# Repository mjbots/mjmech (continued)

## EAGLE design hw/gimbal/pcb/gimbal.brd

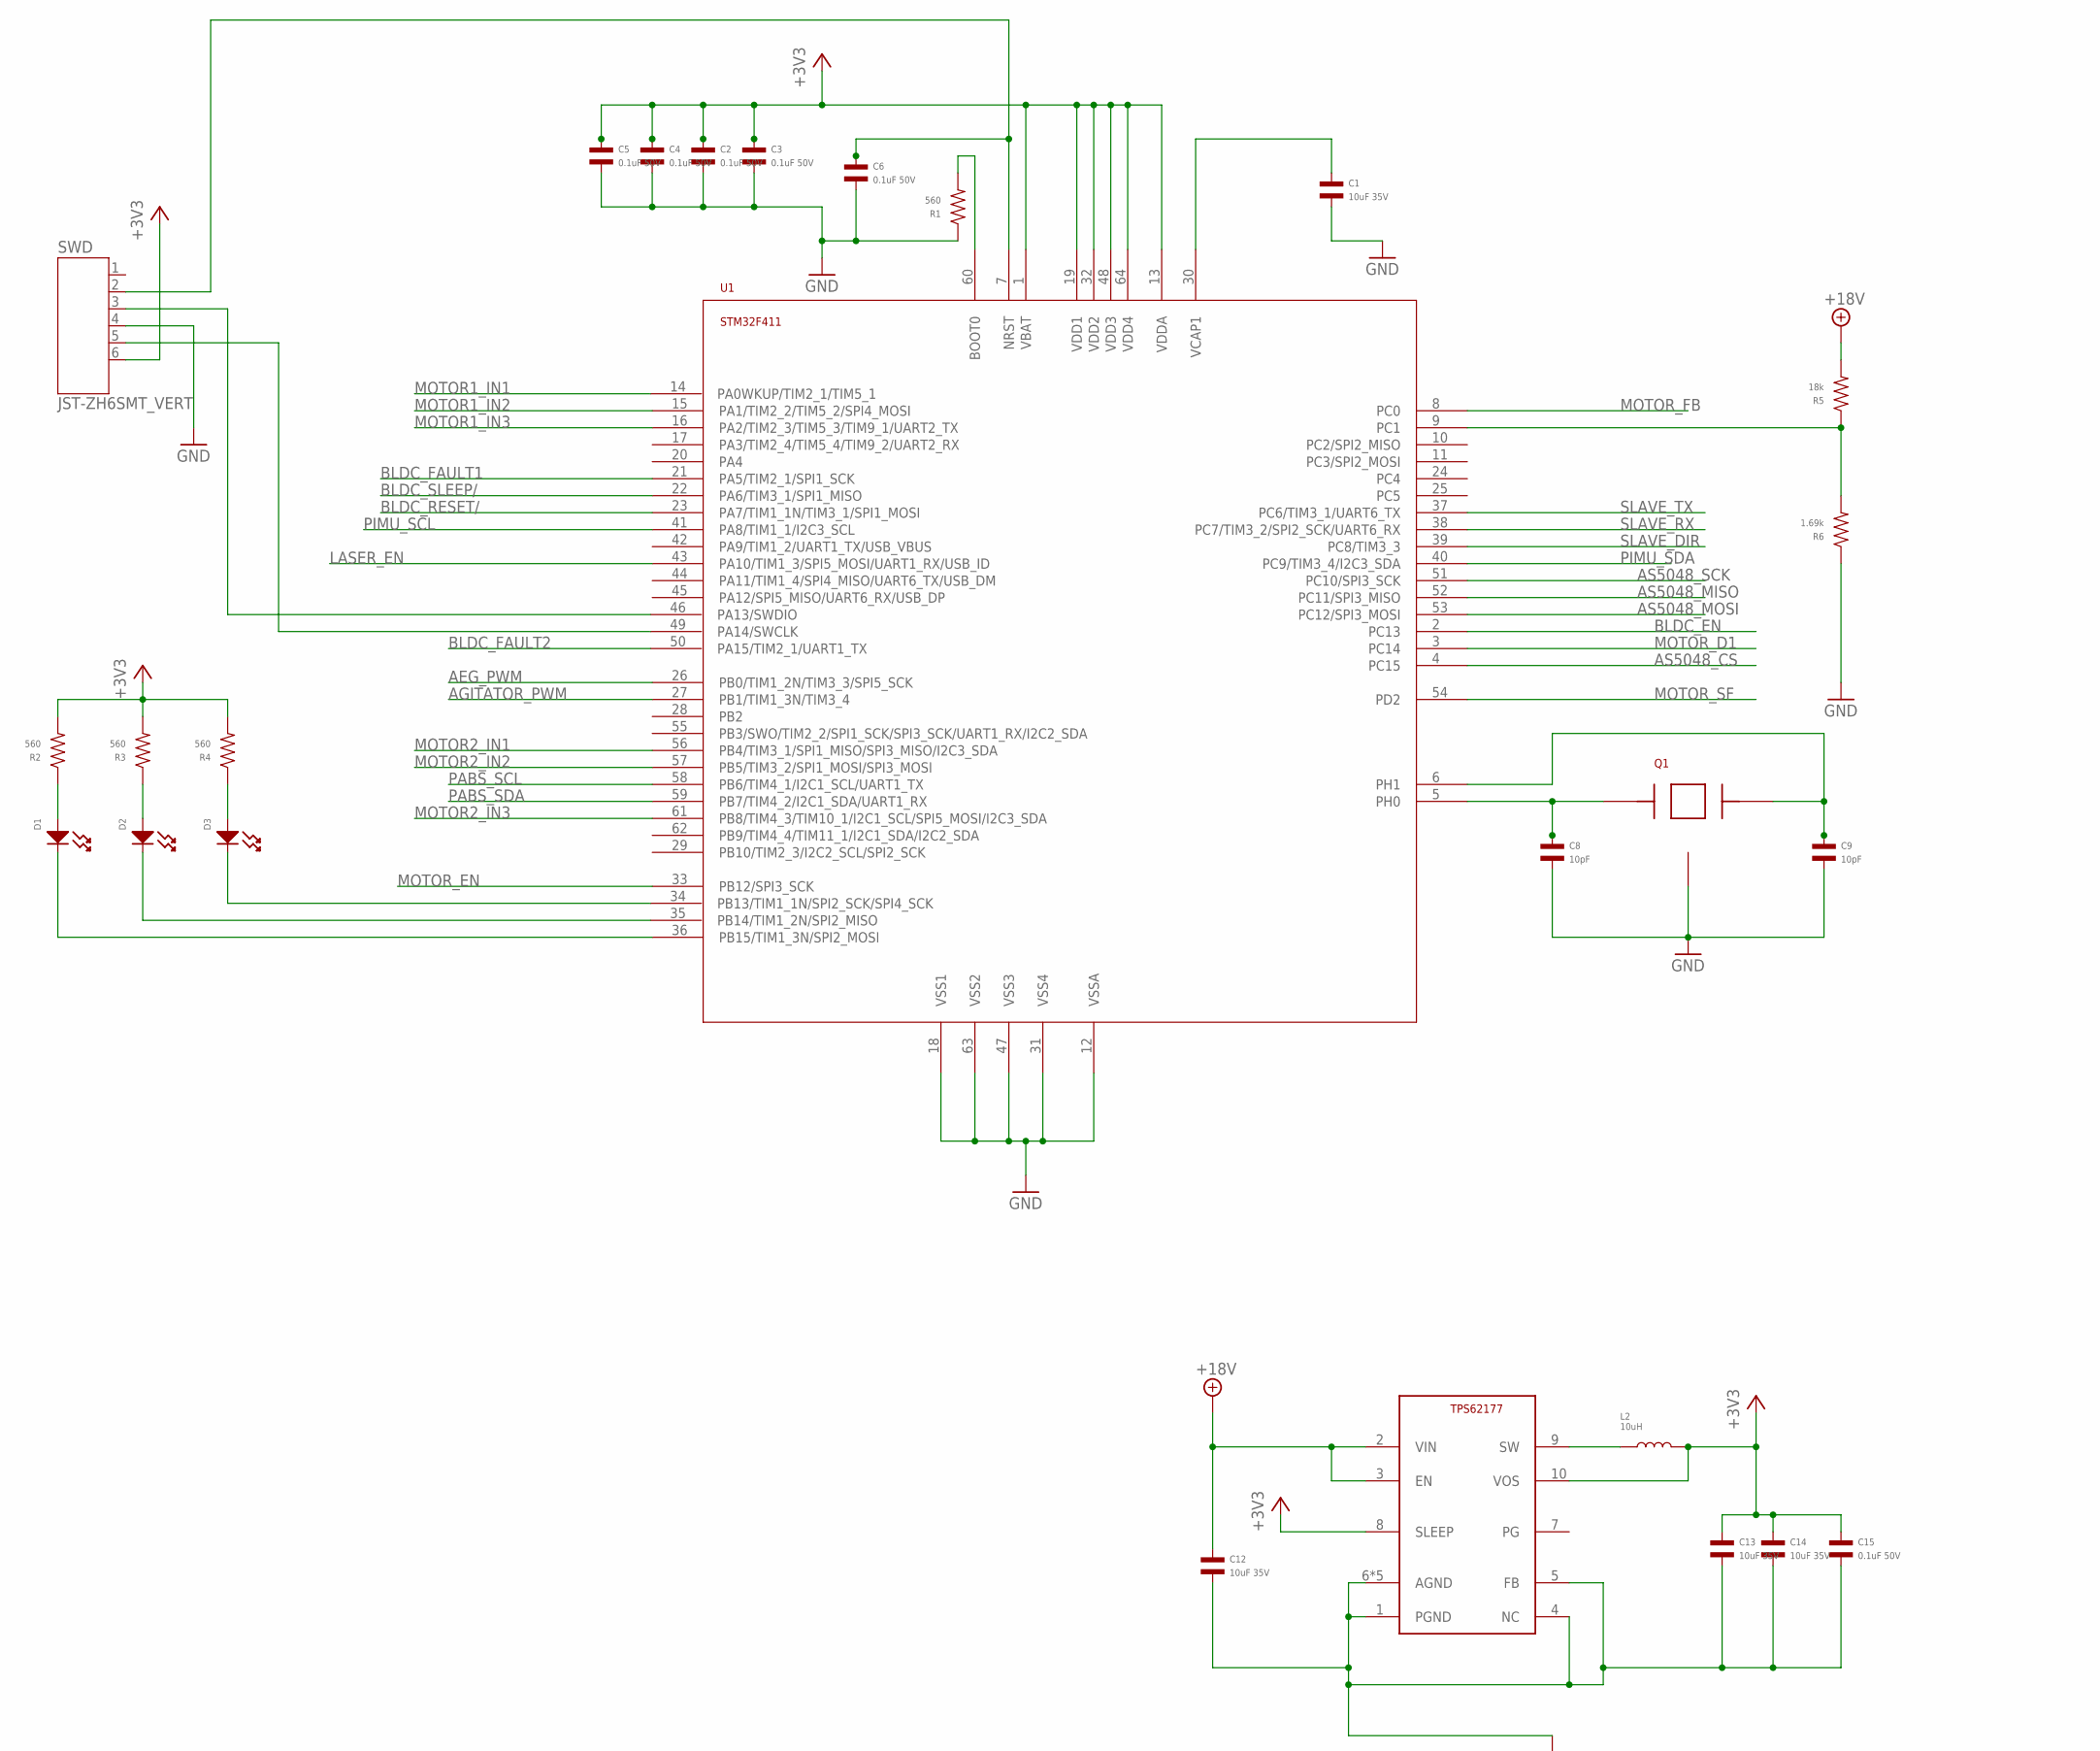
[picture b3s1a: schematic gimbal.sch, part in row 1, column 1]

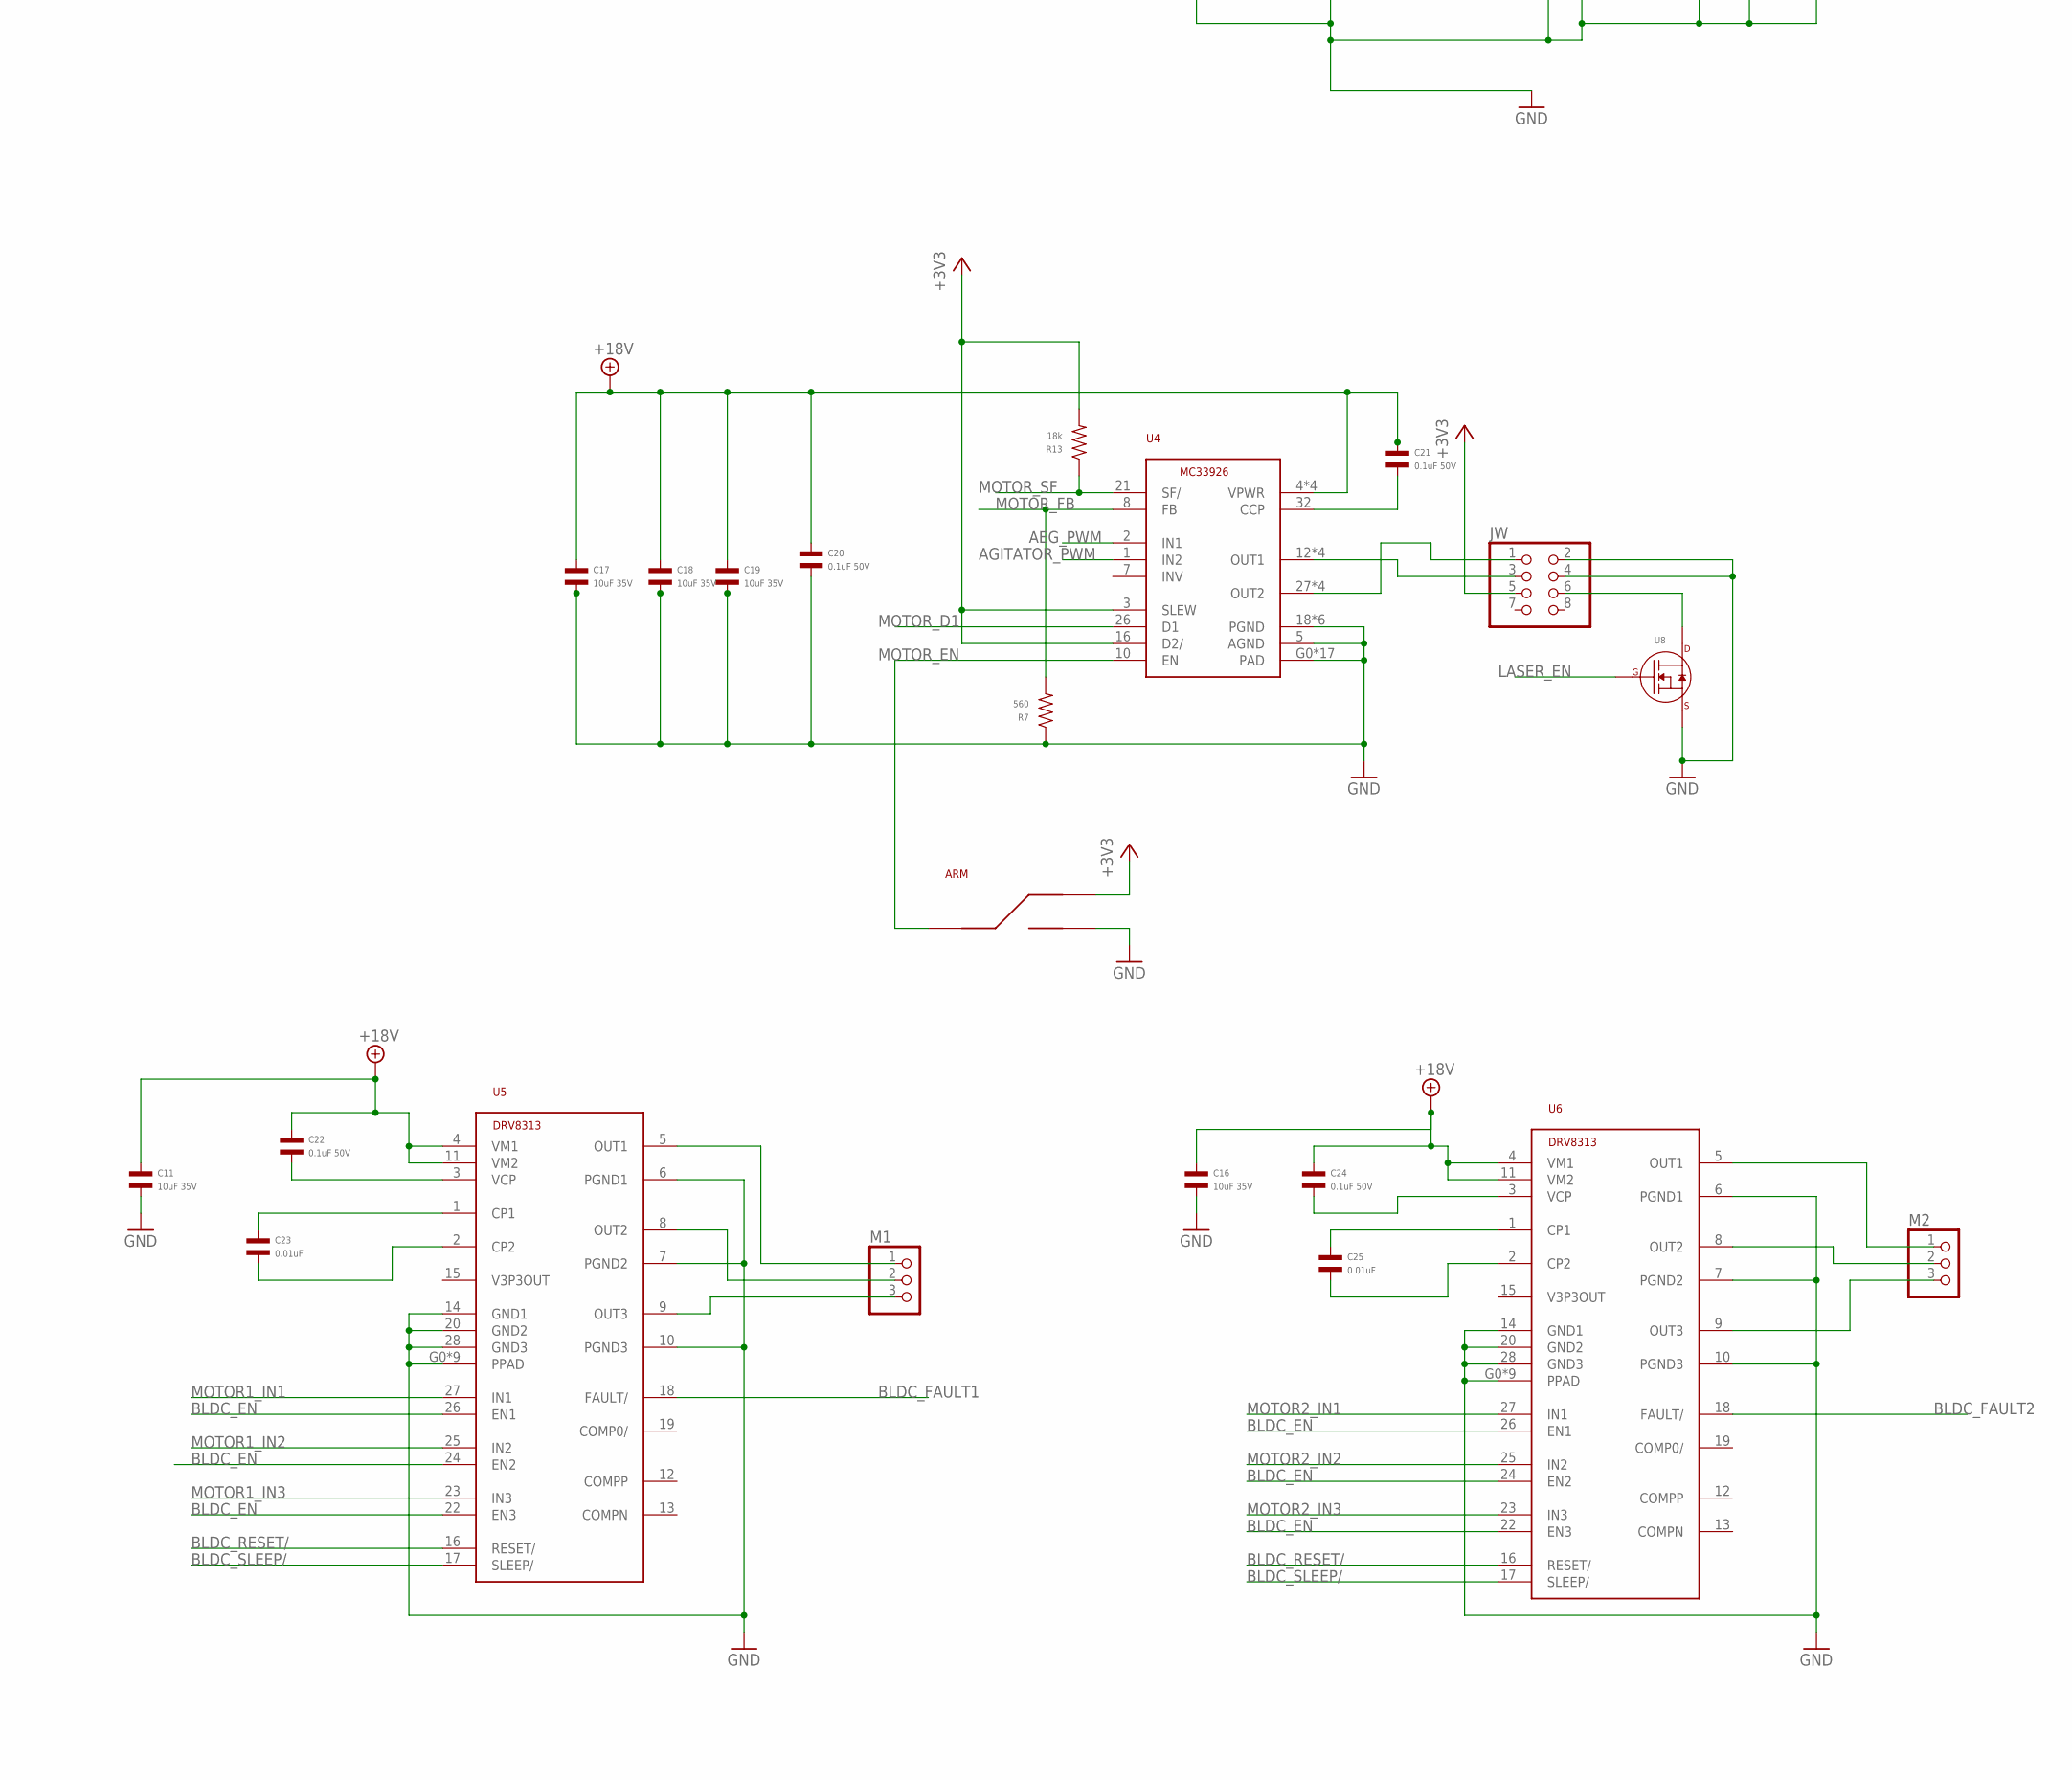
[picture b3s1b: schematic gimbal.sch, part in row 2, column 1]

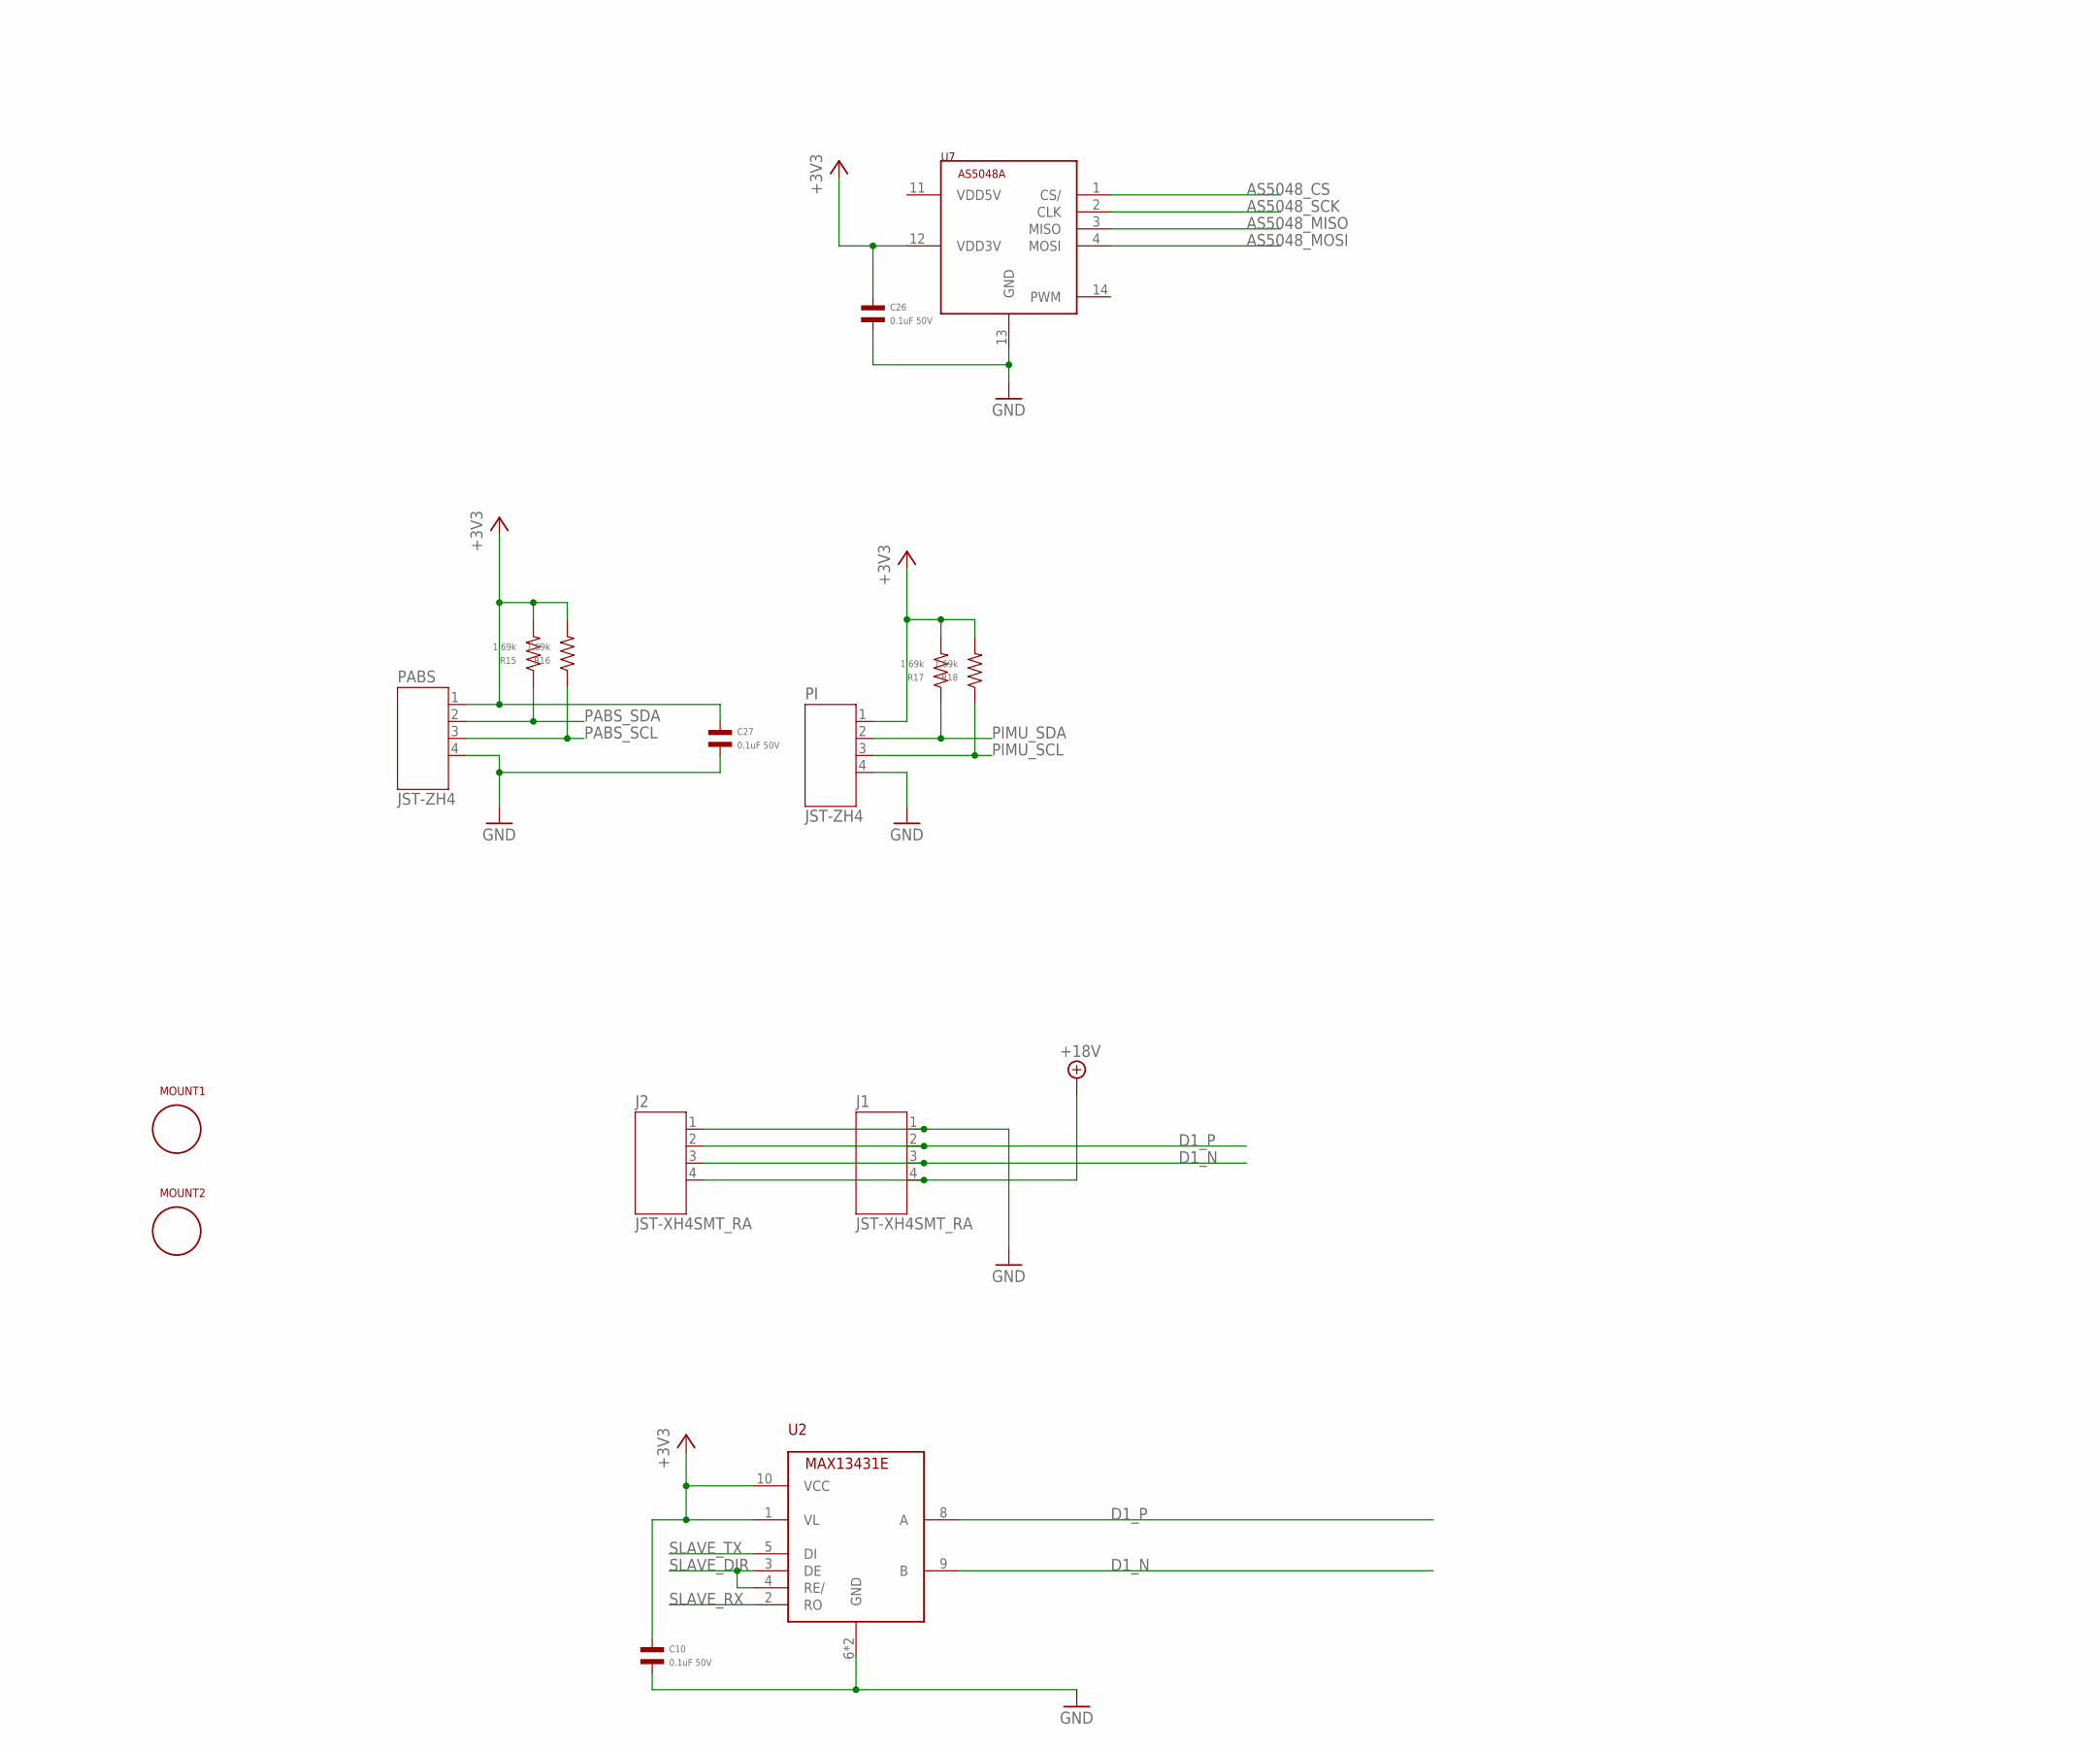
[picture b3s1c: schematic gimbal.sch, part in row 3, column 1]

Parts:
ARM: SLIDE_SWITCHJS_SUB_SWITCH; JS_SUB_SWITCH; MPN JS102011SAQN
C1, C11, C12, C13, C14, C16, C17, C18, C19: 10uF 35V; C1206; MPN CGA5L1X7R1V106M160AE
C2, C3, C4, C5, C6, C10, C15, C20, C21, C22, C24, C26, C27: 0.1uF 50V; C0402; MPN 0402B104K500CT
C8, C9: 10pF; C0603; MPN MF-CAP-0603-10pF
C23, C25: 0.01uF; C0603; MPN MF-CAP-0603-0.01uF
D1, D2, D3: LED_SINGLE-0603-RED; LED0603
J1, J2: JST-XH4SMT_RA; JST_XH_SMT_RA_4; MPN S4B-XH-SM4-TB(LF)(SN)
JW: PINHD-2X4; 2X04
L2: 10uH; L1210; MPN MF-IND-1210-10uH
M1, M2: PINHD-1X3; 1X03
MOUNT1, MOUNT2: M3_MOTOR_MOUNT
PABS: JST-ZH4; JST_ZH_SMT_VERT_4; MPN B4B-ZR-SM4-TF(LF)(SN)
PI: JST-ZH4; JST_ZH_SMT_VERT_4; MPN B4B-ZR-SM4-TF(LF)(SN)
Q1: CRYSTALABM3B; ABM3B; MPN ABM3B-8.000MHZ-10-1-U-T
R1, R2, R3, R4, R7: 560; R0603; MPN MF-RES-0603-560
R5, R13: 18k; R0603; MPN MF-RES-0603-18K
R6, R15, R16, R17, R18: 1.69k; R0603; MPN MF-RES-0603-1.69K
SWD: JST-ZH6SMT_VERT; JST_B6B-ZR-SM4-TF(LF)(SN); MPN B6B-ZR-SM4-TF(LF)(SN)
U1: STM32F4R_64PIN; LQFP64; MPN STM32F411RET6
U2: MAX13431E; TDFN10; MPN MAX13431EETB+T
U3: TPS62177WSON10; WSON10; MPN TPS62177DQCR
U4: MC33926; PQFN32; MPN MC33926PNBR2
U5, U6: DRV8313; HTSSOP28; MPN DRV8313PWP
U7: AS5048A; TSSOP14; MPN AS5047P-ATSM
U8: N-CHANNEL_FET_SOT-23-3; SOT-23-3; MPN MF-DSC-SOT233-BSS138

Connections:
+3V3: ARM.1, C2.P$1, C3.P$1, C4.P$1, C5.P$1, C10.P$1, C13.P$1, C14.P$1, C15.P$1, C26.P$1, C27.P$1, JW.5, L2.P$2, PABS.1, PI.1, R2.P$2, R3.P$2, R4.P$2, R13.P$2, R15.P$2, R16.P$2, R17.P$2, R18.P$2, SWD.6, U1.1 (VBAT), U1.13 (VDDA), U1.19 (VDD1), U1.32 (VDD2), U1.48 (VDD3), U1.64 (VDD4), U2.1 (VL), U2.10 (VCC), U3.8 (SLEEP), U3.10 (VOS), U4.3 (SLEW), U4.16 (D2/), U7.12 (VDD3V)
+18V: C11.P$1, C12.P$1, C16.P$1, C17.P$1, C18.P$1, C19.P$1, C20.P$1, C21.P$1, C22.P$1, C24.P$1, J1.4, J2.4, R5.P$2, U3.2 (VIN), U3.3 (EN), U4.4 (VPWR), U4.6 (VPWR), U4.11 (VPWR), U4.31 (VPWR), U5.4 (VM1), U5.11 (VM2), U6.4 (VM1), U6.11 (VM2)
AEG_PWM: U1.26 (PB0/TIM1_2N/TIM3_3/SPI5_SCK), U4.2 (IN1)
AGITATOR_PWM: U1.27 (PB1/TIM1_3N/TIM3_4), U4.1 (IN2)
AS5048_CS: U1.4 (PC15), U7.1 (CS/)
AS5048_MISO: U1.52 (PC11/SPI3_MISO), U7.3 (MISO)
AS5048_MOSI: U1.53 (PC12/SPI3_MOSI), U7.4 (MOSI)
AS5048_SCK: U1.51 (PC10/SPI3_SCK), U7.2 (CLK)
BLDC_EN: U1.2 (PC13), U5.22 (EN3), U5.24 (EN2), U5.26 (EN1), U6.22 (EN3), U6.24 (EN2), U6.26 (EN1)
BLDC_FAULT1: U1.21 (PA5/TIM2_1/SPI1_SCK), U5.18 (FAULT/)
BLDC_FAULT2: U1.50 (PA15/TIM2_1/UART1_TX), U6.18 (FAULT/)
BLDC_RESET/: U1.23 (PA7/TIM1_1N/TIM3_1/SPI1_MOSI), U5.16 (RESET/), U6.16 (RESET/)
BLDC_SLEEP/: U1.22 (PA6/TIM3_1/SPI1_MISO), U5.17 (SLEEP/), U6.17 (SLEEP/)
D1_N: J1.3, J2.3, U2.9 (B)
D1_P: J1.2, J2.2, U2.8 (A)
GND: ARM.3, C1.P$2, C2.P$2, C3.P$2, C4.P$2, C5.P$2, C6.P$2, C8.P$2, C9.P$2, C10.P$2, C11.P$2, C12.P$2, C13.P$2, C14.P$2, C15.P$2, C16.P$2, C17.P$2, C18.P$2, C19.P$2, C20.P$2, C26.P$2, C27.P$2, J1.1, J2.1, JW.2, JW.4, PABS.4, PI.4, Q1.2, Q1.4, R1.P$1, R6.P$1, R7.P$1, SWD.4, U1.12 (VSSA), U1.18 (VSS1), U1.31 (VSS4), U1.47 (VSS3), U1.63 (VSS2), U2.6 (GND), U2.PAD (GND), U3.1 (PGND), U3.4 (NC), U3.5 (FB), U3.6 (AGND), U3.P0 (AGND), U3.P1 (AGND), U3.P2 (AGND), U3.P3 (AGND), U4.5 (AGND), U4.18 (PGND), U4.19 (PGND), U4.20 (PGND), U4.22 (PGND), U4.23 (PGND), U4.24 (PGND), U4.G0 (PAD), U4.G1 (PAD), U4.G2 (PAD), U4.G3 (PAD), U4.G4 (PAD), U4.G5 (PAD), U4.G6 (PAD), U4.G7 (PAD), U4.G8 (PAD), U4.G9 (PAD), U4.G10 (PAD), U4.G11 (PAD), U4.G12 (PAD), U4.G13 (PAD), U4.G14 (PAD), U4.G15 (PAD), U4.G16 (PAD), U5.6 (PGND1), U5.7 (PGND2), U5.10 (PGND3), U5.14 (GND1), U5.20 (GND2), U5.28 (GND3), U5.G0 (PPAD), U5.G1 (PPAD), U5.G2 (PPAD), U5.G3 (PPAD), U5.G4 (PPAD), U5.G5 (PPAD), U5.G6 (PPAD), U5.G7 (PPAD), U5.G8 (PPAD), U6.6 (PGND1), U6.7 (PGND2), U6.10 (PGND3), U6.14 (GND1), U6.20 (GND2), U6.28 (GND3), U6.G0 (PPAD), U6.G1 (PPAD), U6.G2 (PPAD), U6.G3 (PPAD), U6.G4 (PPAD), U6.G5 (PPAD), U6.G6 (PPAD), U6.G7 (PPAD), U6.G8 (PPAD), U7.13 (GND), U8.P$2 (SOURCE)
LASER_EN: U1.43 (PA10/TIM1_3/SPI5_MOSI/UART1_RX/USB_ID), U8.P$1 (GATE)
MOTOR1_IN1: U1.14 (PA0WKUP/TIM2_1/TIM5_1), U5.27 (IN1)
MOTOR1_IN2: U1.15 (PA1/TIM2_2/TIM5_2/SPI4_MOSI), U5.25 (IN2)
MOTOR1_IN3: U1.16 (PA2/TIM2_3/TIM5_3/TIM9_1/UART2_TX), U5.23 (IN3)
MOTOR2_IN1: U1.56 (PB4/TIM3_1/SPI1_MISO/SPI3_MISO/I2C3_SDA), U6.27 (IN1)
MOTOR2_IN2: U1.57 (PB5/TIM3_2/SPI1_MOSI/SPI3_MOSI), U6.25 (IN2)
MOTOR2_IN3: U1.61 (PB8/TIM4_3/TIM10_1/I2C1_SCL/SPI5_MOSI/I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), U6.23 (IN3)
MOTOR_D1: U1.3 (PC14), U4.26 (D1)
MOTOR_EN: ARM.2, U1.33 (PB12/SPI3_SCK), U4.10 (EN)
MOTOR_FB: R7.P$2, U1.8 (PC0), U4.8 (FB)
MOTOR_SF: R13.P$1, U1.54 (PD2), U4.21 (SF/)
unnamed: JW.6, U8.P$3 (DRAIN)
unnamed: JW.3, U4.12 (OUT1), U4.13 (OUT1), U4.14 (OUT1), U4.15 (OUT1)
unnamed: JW.1, U4.27 (OUT2), U4.28 (OUT2), U4.29 (OUT2), U4.30 (OUT2)
unnamed: L2.P$1, U3.9 (SW)
unnamed: C21.P$2, U4.32 (CCP)
unnamed: M1.1, U5.5 (OUT1)
unnamed: M1.2, U5.8 (OUT2)
unnamed: M1.3, U5.9 (OUT3)
unnamed: M2.1, U6.5 (OUT1)
unnamed: M2.2, U6.8 (OUT2)
unnamed: M2.3, U6.9 (OUT3)
unnamed: C1.P$1, U1.30 (VCAP1)
unnamed: C6.P$1, SWD.2, U1.7 (NRST)
unnamed: C25.P$1, U6.1 (CP1)
unnamed: C25.P$2, U6.2 (CP2)
unnamed: C23.P$2, U5.2 (CP2)
unnamed: C23.P$1, U5.1 (CP1)
unnamed: C22.P$2, U5.3 (VCP)
unnamed: C24.P$2, U6.3 (VCP)
unnamed: SWD.5, U1.49 (PA14/SWCLK)
unnamed: SWD.3, U1.46 (PA13/SWDIO)
unnamed: R1.P$2, U1.60 (BOOT0)
unnamed: R5.P$1, R6.P$2, U1.9 (PC1)
unnamed: C8.P$1, Q1.1, U1.5 (PH0)
unnamed: C9.P$1, Q1.3, U1.6 (PH1)
unnamed: D2.CATHODE, U1.35 (PB14/TIM1_2N/SPI2_MISO)
unnamed: D1.ANODE, R2.P$1
unnamed: D2.ANODE, R3.P$1
unnamed: D3.ANODE, R4.P$1
unnamed: D3.CATHODE, U1.34 (PB13/TIM1_1N/SPI2_SCK/SPI4_SCK)
unnamed: D1.CATHODE, U1.36 (PB15/TIM1_3N/SPI2_MOSI)
PABS_SCL: PABS.3, R16.P$1, U1.58 (PB6/TIM4_1/I2C1_SCL/UART1_TX)
PABS_SDA: PABS.2, R15.P$1, U1.59 (PB7/TIM4_2/I2C1_SDA/UART1_RX)
PIMU_SCL: PI.3, R18.P$1, U1.41 (PA8/TIM1_1/I2C3_SCL)
PIMU_SDA: PI.2, R17.P$1, U1.40 (PC9/TIM3_4/I2C3_SDA)
SLAVE_DIR: U1.39 (PC8/TIM3_3), U2.3 (DE), U2.4 (RE/)
SLAVE_RX: U1.38 (PC7/TIM3_2/SPI2_SCK/UART6_RX), U2.2 (RO)
SLAVE_TX: U1.37 (PC6/TIM3_1/UART6_TX), U2.5 (DI)

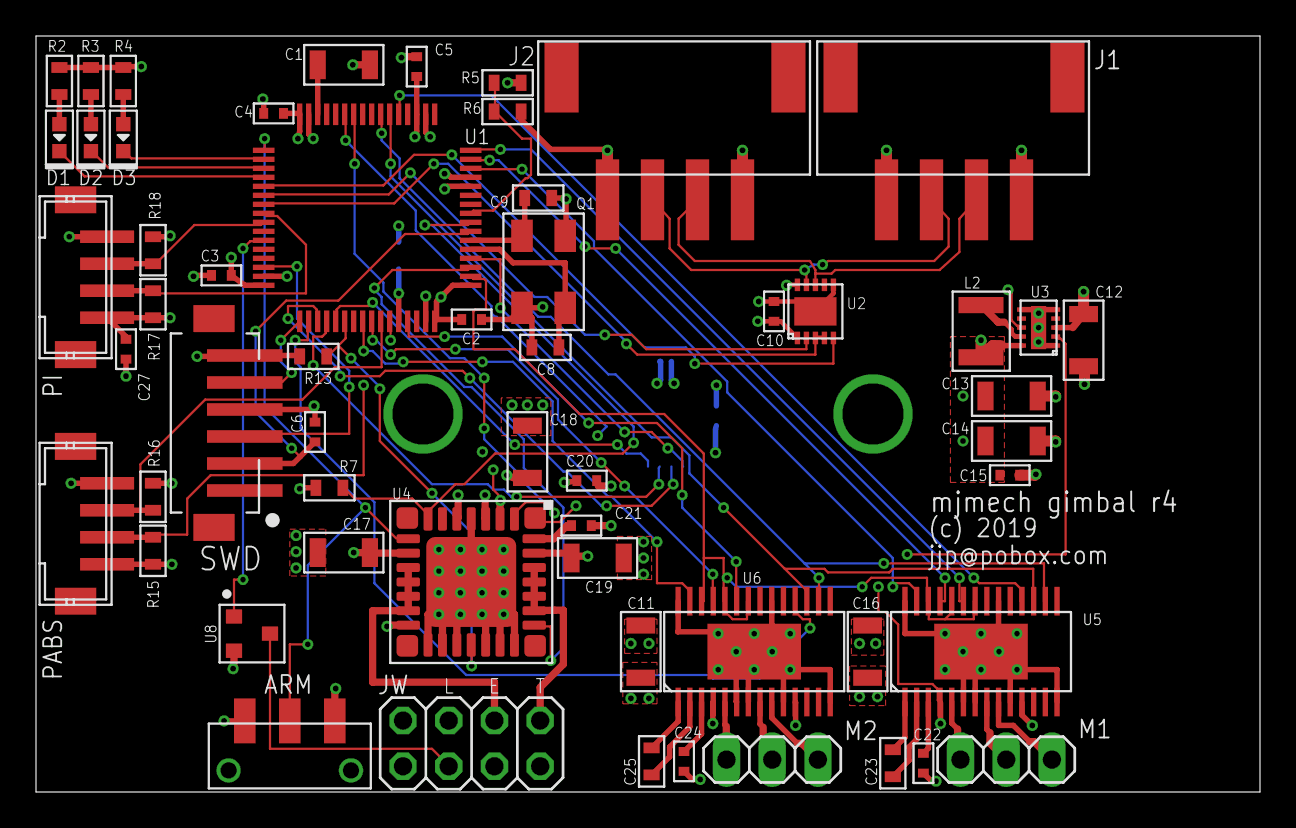
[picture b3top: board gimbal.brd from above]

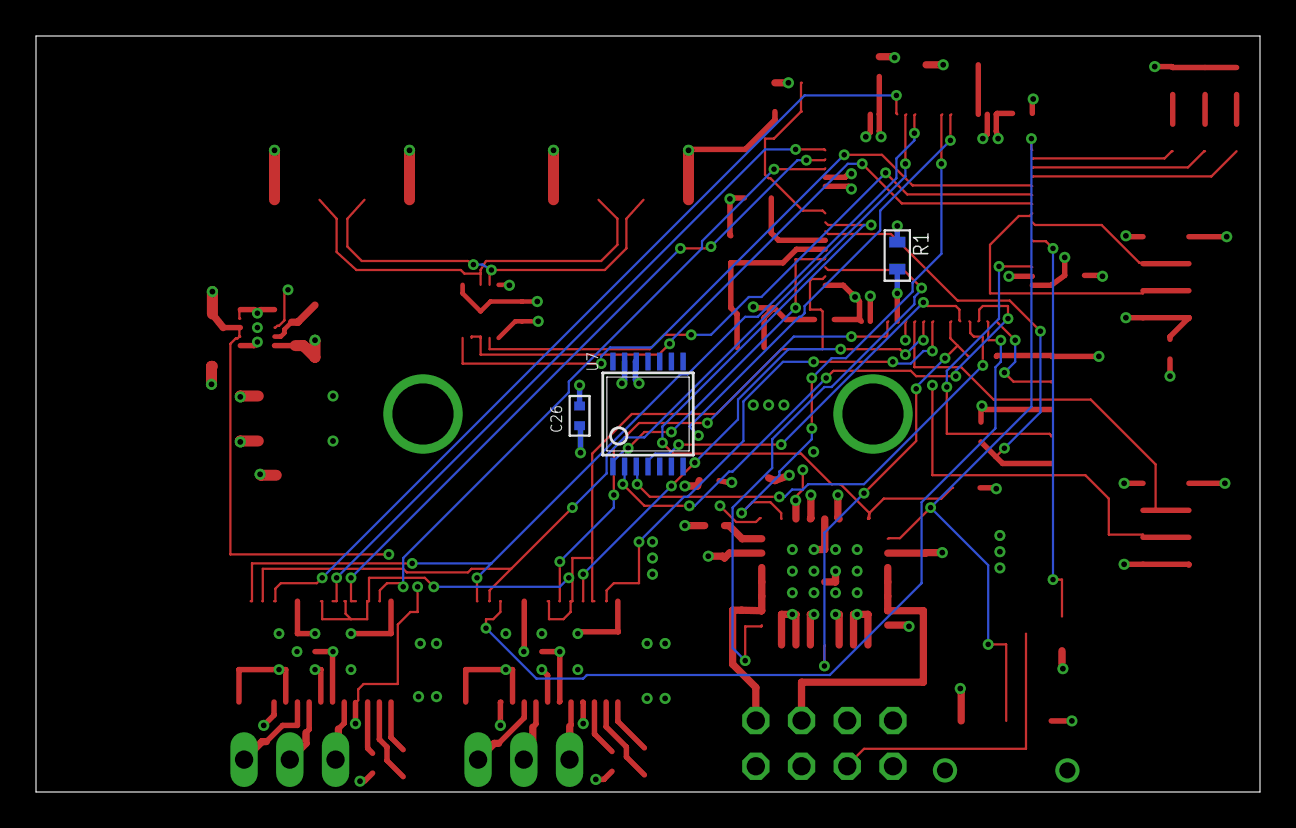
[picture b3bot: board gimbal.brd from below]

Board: 4 copper layers, 68.0 x 42.0 mm, 62 parts (3 on the bottom side), 65 nets.

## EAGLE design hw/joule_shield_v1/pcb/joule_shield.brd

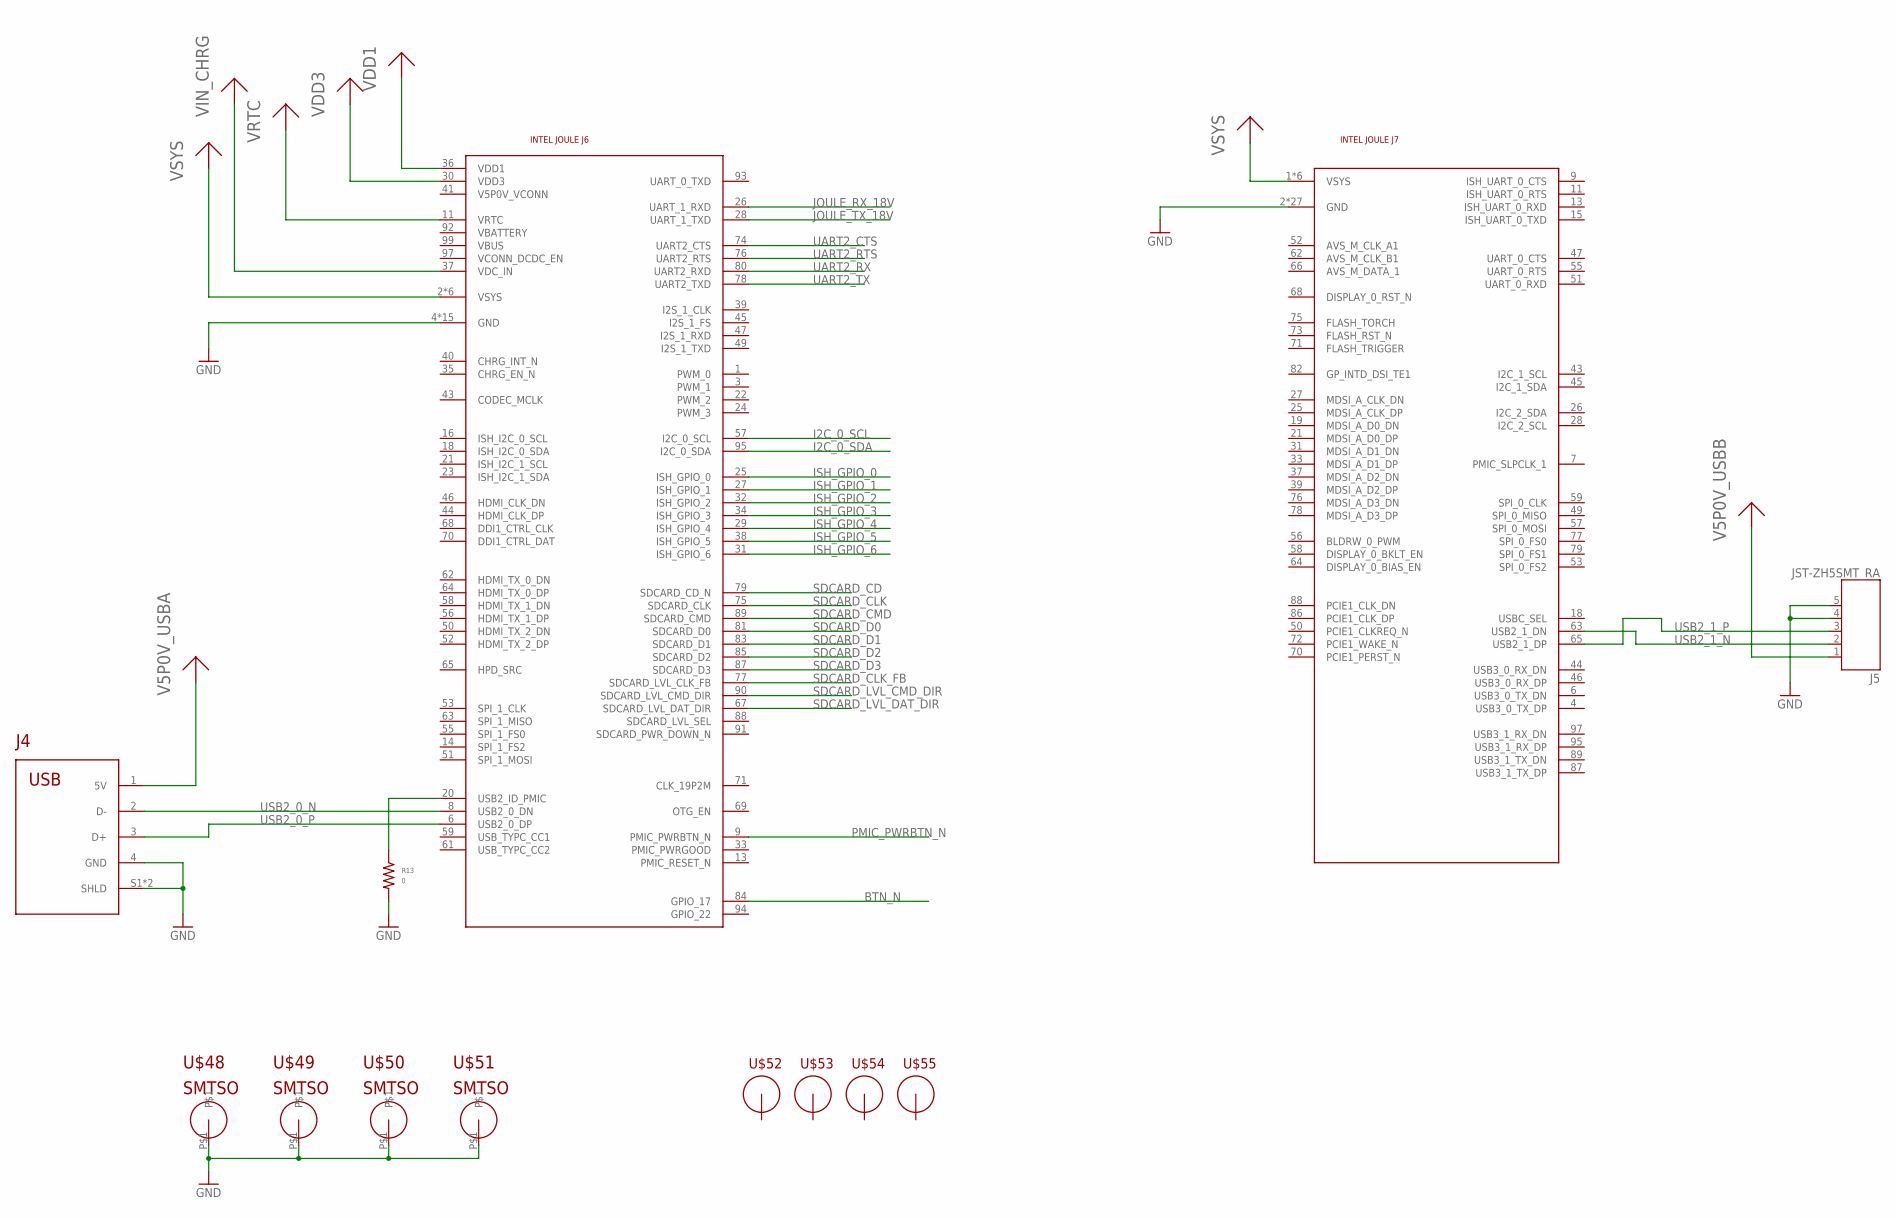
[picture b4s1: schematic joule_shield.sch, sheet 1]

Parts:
J4: USB_AUSB_A_SMT_RA; USB_RECPT_87583; MPN 87583-2010BLF
J5: JST-ZH5SMT_RA; JST_ZH_SMT_RA_5; MPN S5B-ZR-SM4A-TF(LF)(SN)
J6: INTEL_JOULE_J6; HIROSE-40C-100DS; MPN DF40C-100DS-0.4V(51)
J7: INTEL_JOULE_J7; HIROSE-40C-100DS; MPN DF40C-100DS-0.4V(51)
R13: 0; R0603; MPN MF-RES-0603-0
U$48, U$49, U$50, U$51: SMTSOSMTSO-M1.6; SMTSO-M1.6
U$52, U$53, U$54, U$55: M2.5MOUNT

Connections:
BTN_N: J6.84 (GPIO_17); also elsewhere on the board
GND: J4.4 (GND), J4.S1 (SHLD), J4.S2 (SHLD), J5.4, J5.5, J6.4 (GND), J6.10 (GND), J6.19 (GND), J6.42 (GND), J6.48 (GND), J6.54 (GND), J6.60 (GND), J6.66 (GND), J6.72 (GND), J6.73 (GND), J6.82 (GND), J6.86 (GND), J6.96 (GND), J6.98 (GND), J6.100 (GND), J7.2 (GND), J7.5 (GND), J7.8 (GND), J7.10 (GND), J7.16 (GND), J7.17 (GND), J7.23 (GND), J7.24 (GND), J7.29 (GND), J7.30 (GND), J7.35 (GND), J7.36 (GND), J7.41 (GND), J7.42 (GND), J7.54 (GND), J7.60 (GND), J7.61 (GND), J7.67 (GND), J7.74 (GND), J7.80 (GND), J7.84 (GND), J7.85 (GND), J7.90 (GND), J7.91 (GND), J7.93 (GND), J7.96 (GND), J7.99 (GND), R13.P$2, U$48.P$1, U$49.P$1, U$50.P$1, U$51.P$1; also elsewhere on the board
I2C_0_SCL: J6.57 (I2C_0_SCL); also elsewhere on the board
I2C_0_SDA: J6.95 (I2C_0_SDA); also elsewhere on the board
ISH_GPIO_0: J6.25 (ISH_GPIO_0); also elsewhere on the board
ISH_GPIO_1: J6.27 (ISH_GPIO_1); also elsewhere on the board
ISH_GPIO_2: J6.32 (ISH_GPIO_2); also elsewhere on the board
ISH_GPIO_3: J6.34 (ISH_GPIO_3); also elsewhere on the board
ISH_GPIO_4: J6.29 (ISH_GPIO_4); also elsewhere on the board
ISH_GPIO_5: J6.38 (ISH_GPIO_5); also elsewhere on the board
ISH_GPIO_6: J6.31 (ISH_GPIO_6); also elsewhere on the board
JOULE_RX_18V: J6.26 (UART_1_RXD); also elsewhere on the board
JOULE_TX_18V: J6.28 (UART_1_TXD); also elsewhere on the board
unnamed: J6.20 (USB2_ID_PMIC), R13.P$1
PMIC_PWRBTN_N: J6.9 (PMIC_PWRBTN_N); also elsewhere on the board
SDCARD_CD: J6.79 (SDCARD_CD_N); also elsewhere on the board
SDCARD_CLK: J6.75 (SDCARD_CLK); also elsewhere on the board
SDCARD_CLK_FB: J6.77 (SDCARD_LVL_CLK_FB); also elsewhere on the board
SDCARD_CMD: J6.89 (SDCARD_CMD); also elsewhere on the board
SDCARD_D0: J6.81 (SDCARD_D0); also elsewhere on the board
SDCARD_D1: J6.83 (SDCARD_D1); also elsewhere on the board
SDCARD_D2: J6.85 (SDCARD_D2); also elsewhere on the board
SDCARD_D3: J6.87 (SDCARD_D3); also elsewhere on the board
SDCARD_LVL_CMD_DIR: J6.90 (SDCARD_LVL_CMD_DIR); also elsewhere on the board
SDCARD_LVL_DAT_DIR: J6.67 (SDCARD_LVL_DAT_DIR); also elsewhere on the board
UART2_CTS: J6.74 (UART2_CTS); also elsewhere on the board
UART2_RTS: J6.76 (UART2_RTS); also elsewhere on the board
UART2_RX: J6.80 (UART2_RXD); also elsewhere on the board
UART2_TX: J6.78 (UART2_TXD); also elsewhere on the board
USB2_0_N: J4.2 (D-), J6.8 (USB2_0_DN)
USB2_0_P: J4.3 (D+), J6.6 (USB2_0_DP)
USB2_1_N: J5.2, J7.63 (USB2_1_DN)
USB2_1_P: J5.3, J7.65 (USB2_1_DP)
V5P0V_USBA: J4.1 (5V); also elsewhere on the board
V5P0V_USBB: J5.1; also elsewhere on the board
VDD1: J6.36 (VDD1); also elsewhere on the board
VDD3: J6.30 (VDD3); also elsewhere on the board
VIN_CHRG: J6.37 (VDC_IN); also elsewhere on the board
VRTC: J6.11 (VRTC); also elsewhere on the board
VSYS: J6.2 (VSYS), J6.5 (VSYS), J6.7 (VSYS), J6.12 (VSYS), J6.15 (VSYS), J6.17 (VSYS), J7.1 (VSYS), J7.3 (VSYS), J7.20 (VSYS), J7.22 (VSYS), J7.32 (VSYS), J7.34 (VSYS); also elsewhere on the board
